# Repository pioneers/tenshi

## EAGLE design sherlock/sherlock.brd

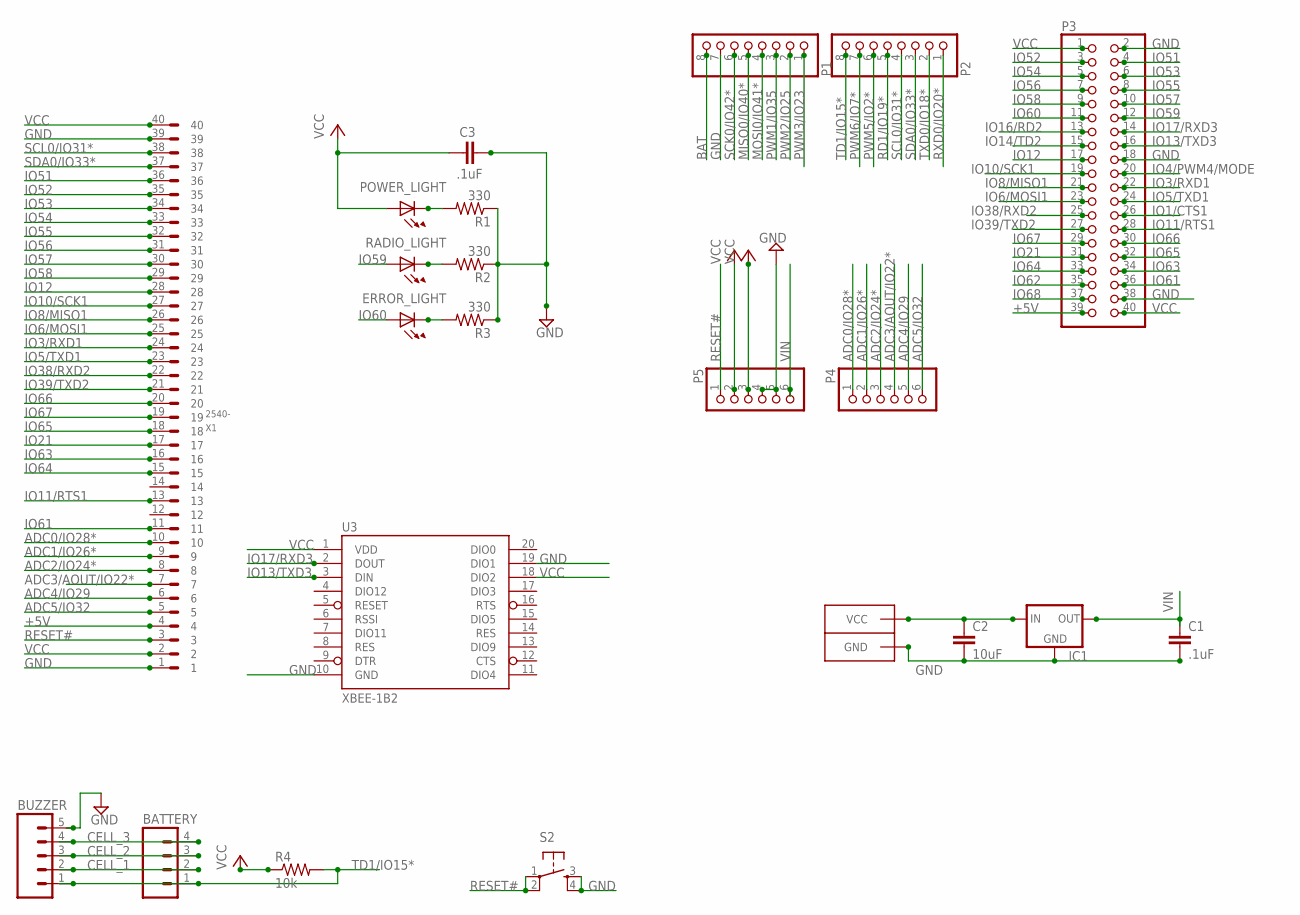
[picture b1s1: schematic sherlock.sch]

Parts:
BATTERY: M041X04-MTA; 1X04-MTA
BUZZER: M05PTH; 1X05
C1, C3: .1uF; 0603-CAP
C2: 10uF; 0603-CAP
ERROR_LIGHT: LED0805; LED-0805
IC1: V_REG_78XXSIDE; 78XXL
P1, P2: PINHD-1X8; 1X08
P3: PINHD-2X20; 2X20
P4, P5: PINHD-1X6; 1X06
POWER: ANDERSONHORIZONTAL; ANDERSON_HORIZONTAL
POWER_LIGHT: LED0805; LED-0805
R1, R2, R3: 330; R0603
R4: 10k; R0603
RADIO_LIGHT: LED0805; LED-0805
S2: TAC_SWITCHPTH; TACTILE-PTH
U3: XBEE-1B2; XBEE-SILK
X1: 2540-; PAK100/2500-40

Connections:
12V: C2.1, IC1.IN, POWER.PIN2 (VCC)
+5V: P3.39, P5.3, X1.4
ADC0/IO28*: P4.1, X1.10
ADC1/IO26*: P4.2, X1.9
ADC2/IO24*: P4.3, X1.8
ADC3/AOUT/IO22*: P4.4, X1.7
ADC4/IO29: P4.5, X1.6
ADC5/IO32: P4.6, X1.5
BAT: P1.8
CELL_1: BATTERY.2, BUZZER.2
CELL_2: BATTERY.3, BUZZER.3
CELL_3: BATTERY.4, BUZZER.4
GND: BUZZER.5, C1.2, C2.2, C3.2, IC1.GND, P1.7, P3.2, P3.18, P3.38, P5.4, P5.5, POWER.PIN1 (GND), R1.1, R2.1, R3.1, S2.3, S2.4, U3.10 (GND), U3.19 (DIO1), X1.1, X1.39
IO1/CTS1: P3.26
IO3/RXD1: P3.22, X1.24
IO4/PWM4/MODE: P3.20
IO5/TXD1: P3.24, X1.23
IO6/MOSI1: P3.23, X1.25
IO8/MISO1: P3.21, X1.26
IO10/SCK1: P3.19, X1.27
IO11/RTS1: P3.28, X1.13
IO12: P3.17, X1.28
IO13/TXD3: P3.16, U3.3 (DIN)
IO14/TD2: P3.15
IO16/RD2: P3.13
IO17/RXD3: P3.14, U3.2 (DOUT)
IO21: P3.31, X1.17
IO38/RXD2: P3.25, X1.22
IO39/TXD2: P3.27, X1.21
IO51: P3.4, X1.36
IO52: P3.3, X1.35
IO53: P3.6, X1.34
IO54: P3.5, X1.33
IO55: P3.8, X1.32
IO56: P3.7, X1.31
IO57: P3.10, X1.30
IO58: P3.9, X1.29
IO59: P3.12, RADIO_LIGHT.A
IO60: ERROR_LIGHT.A, P3.11
IO61: P3.36, X1.11
IO62: P3.35
IO63: P3.34, X1.16
IO64: P3.33, X1.15
IO65: P3.32, X1.18
IO66: P3.30, X1.20
IO67: P3.29, X1.19
IO68: P3.37
MISO0/IO40*: P1.5
MOSI0/IO41*: P1.4
unnamed: POWER_LIGHT.C, R1.2
unnamed: R2.2, RADIO_LIGHT.C
unnamed: ERROR_LIGHT.C, R3.2
PWM1/IO35: P1.3
PWM2/IO25: P1.2
PWM3/IO23: P1.1
PWM5/IO2*: P2.6
PWM6/IO7*: P2.7
RD1/IO19*: P2.5
RESET#: P5.1, S2.1, S2.2, X1.3
RXD0/IO20*: P2.1
SCK0/IO42*: P1.6
SCL0/IO31*: P2.4, X1.38
SDA0/IO33*: P2.3, X1.37
TD1/IO15*: BATTERY.1, BUZZER.1, P2.8, R4.2
TXD0/IO18*: P2.2
VCC: C3.1, P3.1, P3.40, P5.2, POWER_LIGHT.A, R4.1, U3.1 (VDD), U3.18 (DIO2), X1.2, X1.40
VIN: C1.1, IC1.OUT, P5.6

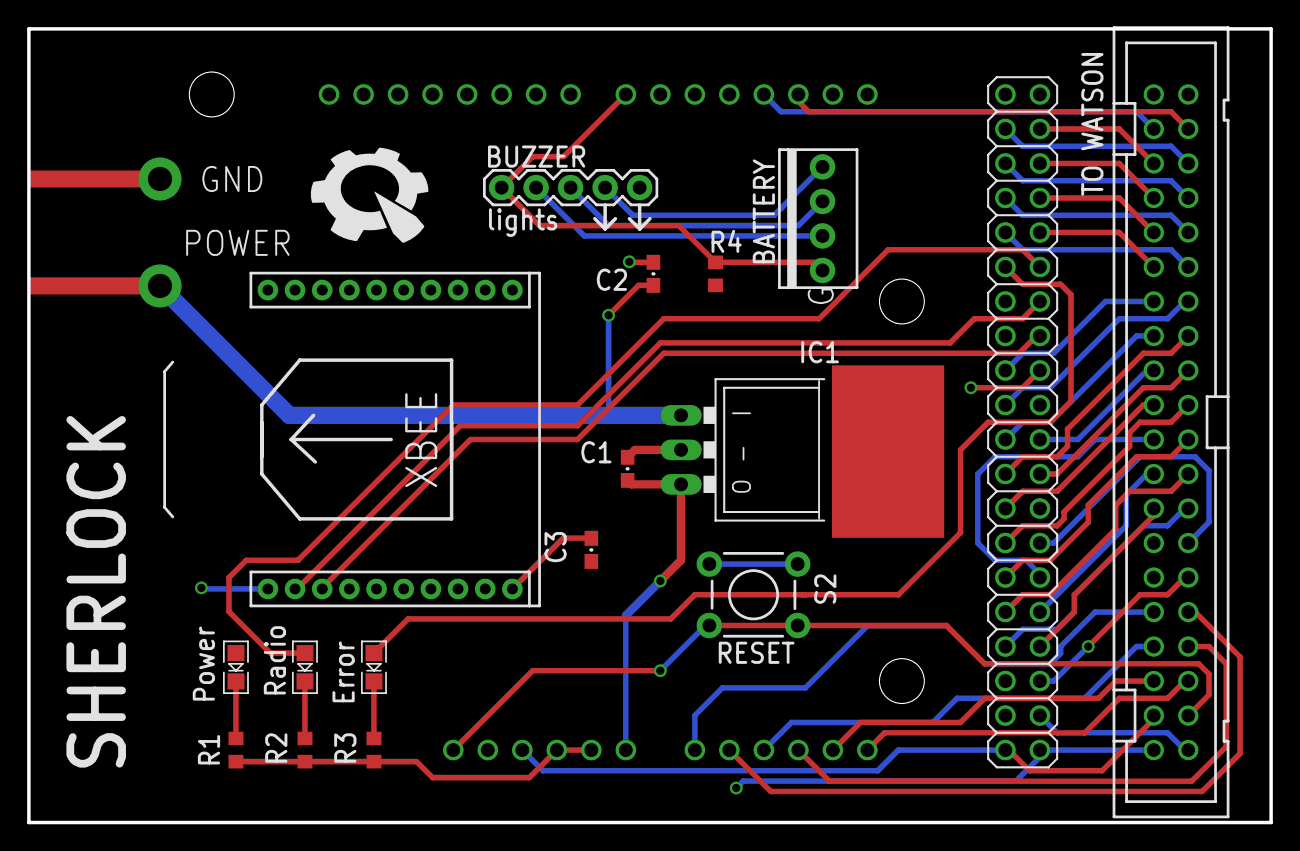
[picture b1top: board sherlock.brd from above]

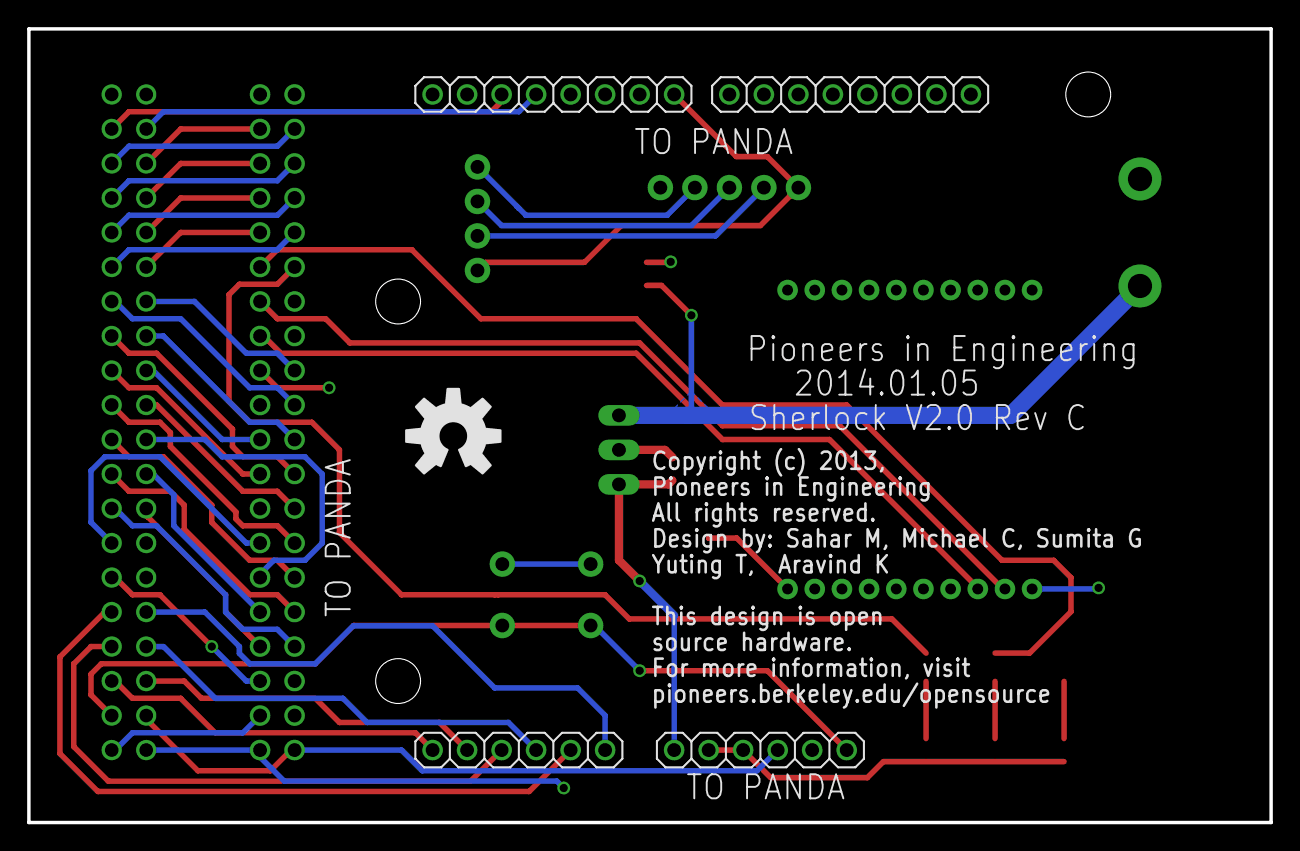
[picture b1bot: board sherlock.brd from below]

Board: 2 copper layers, 91.4 x 58.4 mm, 27 parts (5 on the bottom side), 49 nets.

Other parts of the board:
U$1: PIE-LOGO-SMALL
U$3: Mounting + Test; STAND-OFF
U$4, U$5: Mounting; STAND-OFF
U$7: OSHW-LOGO-L

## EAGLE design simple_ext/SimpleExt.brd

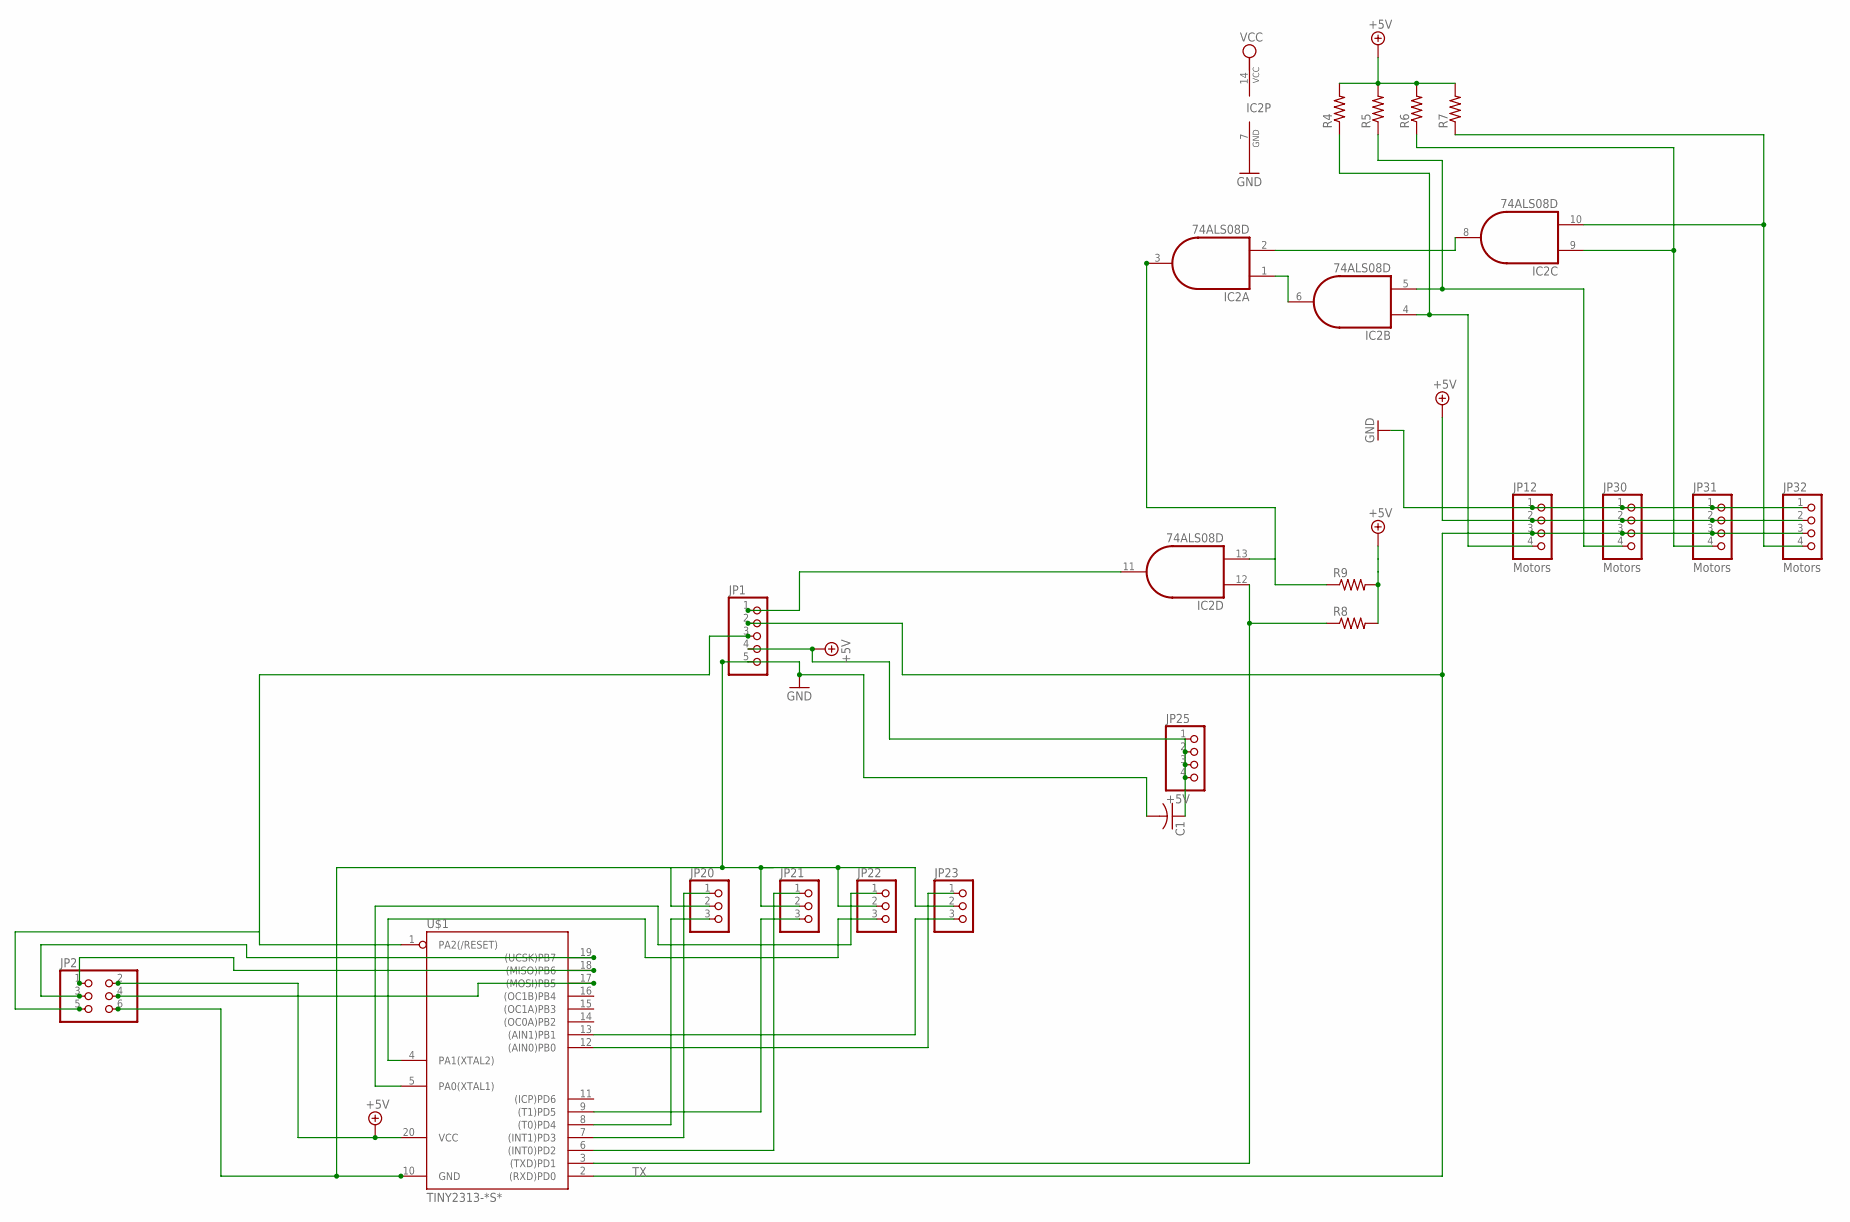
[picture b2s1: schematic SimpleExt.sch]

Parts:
C1: C-USC0603K; C0603K
IC2: 74ALS08D; SO14
JP1: PINHD-1X5; 1X05
JP2: PINHD-2X3; 2X03
JP12, JP30, JP31, JP32: Motors; 1X04-S
JP20, JP21, JP22, JP23: PINHD-1X03_2.54-S; 1X03-S
JP25: +5V; 1X04-S
R4, R5, R6, R7, R8, R9: R-US_R0603; R0603
U$1: TINY2313-*S*; SO20L$

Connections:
+5V: C1.1, JP1.4, JP2.2, JP12.2, JP25.1, JP25.2, JP25.3, JP25.4, JP30.2, JP31.2, JP32.2, R4.2, R5.2, R6.2, R7.2, R8.2, R9.2, U$1.20 (VCC)
GND: C1.2, IC2.7 (GND), JP1.5, JP2.6, JP12.1, JP20.2, JP21.2, JP22.2, JP23.2, JP30.1, JP31.1, JP32.1, U$1.10 (GND)
unnamed: IC2.11 (O), JP1.1
unnamed: JP2.3, U$1.19 ((UCSK)PB7)
unnamed: IC2.10 (I1), JP32.4, R7.1
unnamed: IC2.9 (I0), JP31.4, R6.1
unnamed: JP2.1, U$1.18 ((MISO)PB6)
unnamed: IC2.1 (I0), IC2.6 (O)
unnamed: IC2.2 (I1), IC2.8 (O)
unnamed: IC2.4 (I0), JP12.4, R4.1
unnamed: IC2.12 (I0), R8.1, U$1.3 ((TXD)PD1)
unnamed: JP20.1, U$1.7 ((INT1)PD3)
unnamed: JP21.1, U$1.6 ((INT0)PD2)
unnamed: JP23.3, U$1.13 ((AIN1)PB1)
unnamed: JP20.3, U$1.8 ((T0)PD4)
unnamed: JP21.3, U$1.9 ((T1)PD5)
unnamed: JP2.4, U$1.17 ((MOSI)PB5)
unnamed: JP23.1, U$1.12 ((AIN0)PB0)
unnamed: JP22.3, U$1.4 (PA1(XTAL2))
unnamed: JP22.1, U$1.5 (PA0(XTAL1))
unnamed: IC2.5 (I1), JP30.4, R5.1
RESET#: JP1.3, JP2.5, U$1.1 (PA2(/RESET))
RXD0/IO20*: IC2.3 (O), IC2.13 (I1), R9.1
TX: JP1.2, JP12.3, JP30.3, JP31.3, JP32.3, U$1.2 ((RXD)PD0)
VCC: IC2.14 (VCC)

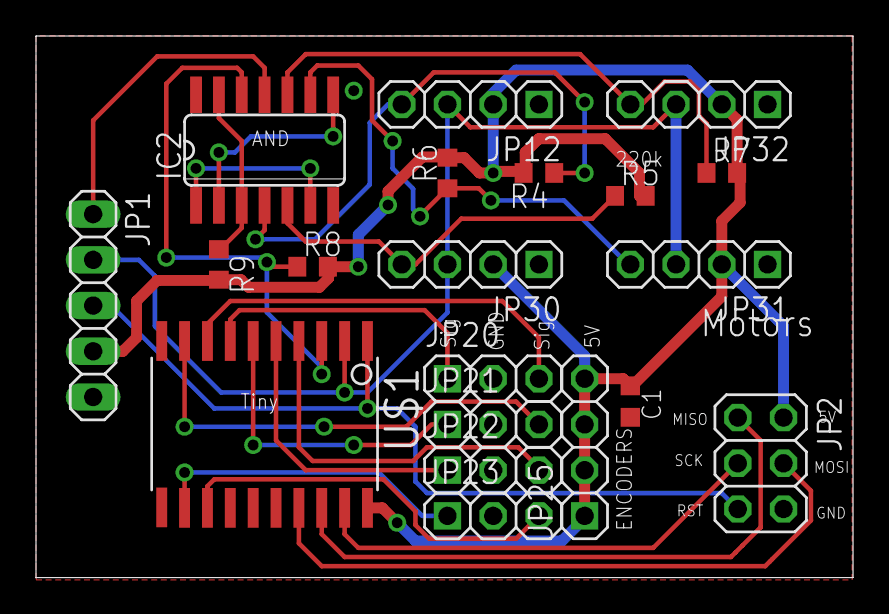
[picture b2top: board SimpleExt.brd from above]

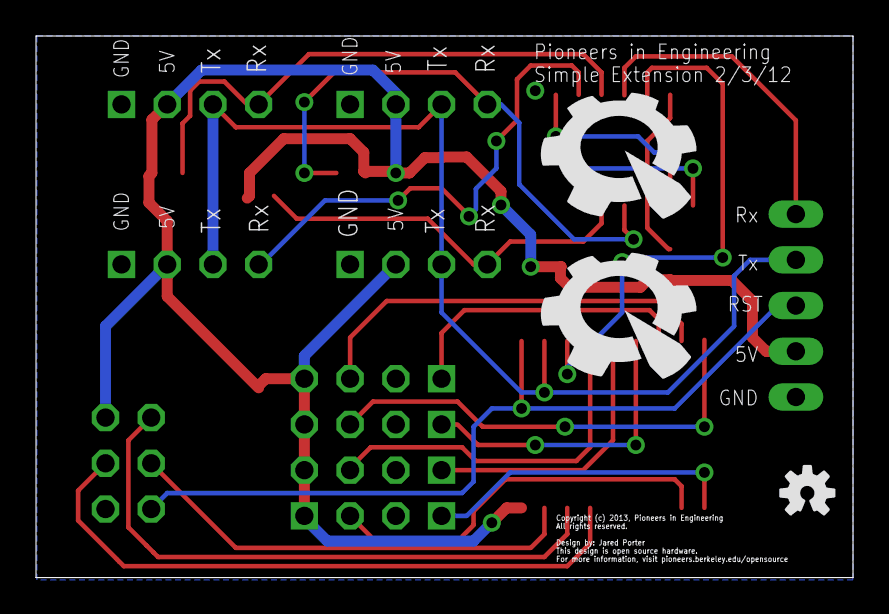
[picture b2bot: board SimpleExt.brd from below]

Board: 2 copper layers, 45.4 x 30.1 mm, 23 parts (3 on the bottom side), 24 nets.

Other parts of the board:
U$2: OSHW-LOGO-S
U$5, U$6: PIE-LOGO-SMALL

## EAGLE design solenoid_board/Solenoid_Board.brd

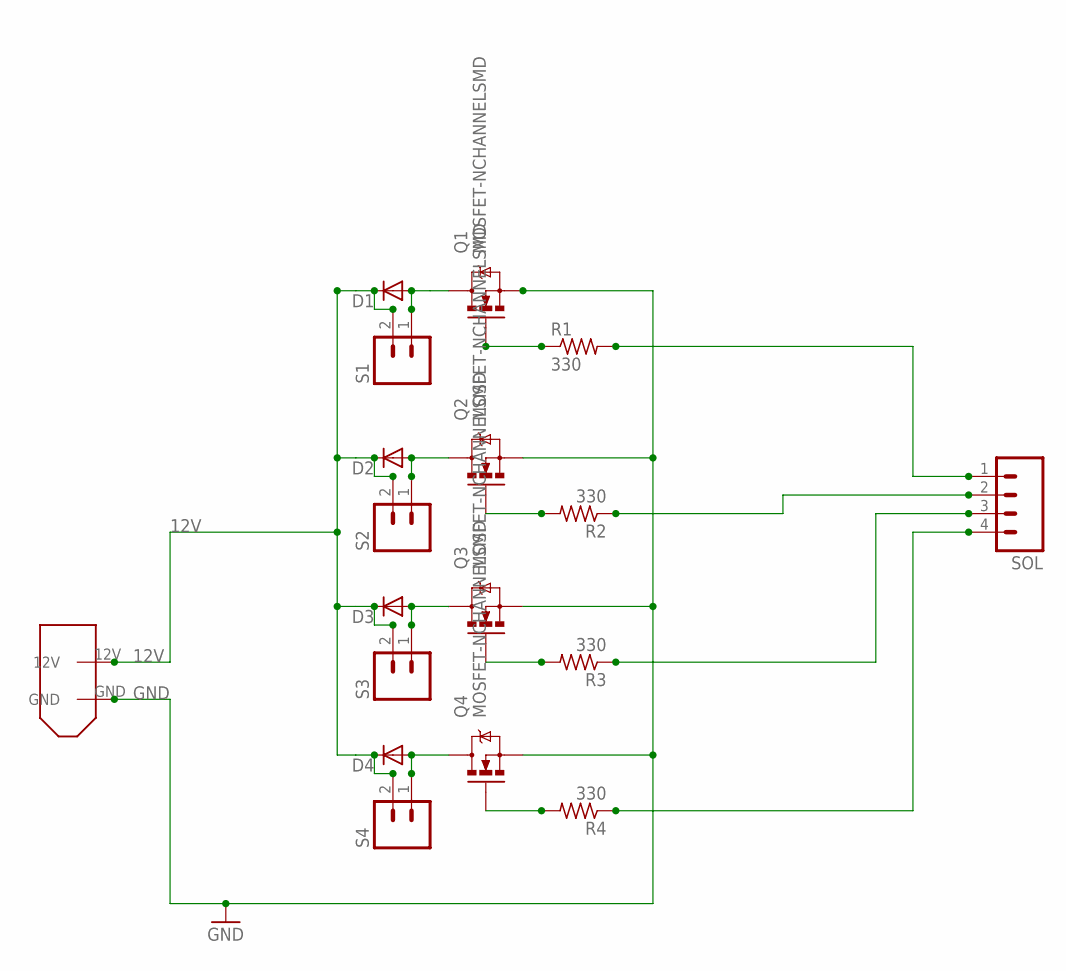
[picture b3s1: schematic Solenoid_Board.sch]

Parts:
D1, D2, D3, D4: DIODESMA-ALT; SMA-DIODE_ALT
Q1, Q2, Q3, Q4: MOSFET-NCHANNELSMD; SOT23-3
R1, R2, R3, R4: 330; R0603
S1, S2, S3, S4: M02; 1X02
SOL: M04; 1X04
U$2: XT60CONNECTOR

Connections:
12V: D1.C, D2.C, D3.C, D4.C, S1.2, S2.2, S3.2, S4.2, U$2.12V
GND: Q1.2 (S), Q2.2 (S), Q3.2 (S), Q4.2 (S), U$2.GND
unnamed: R1.2, SOL.1
unnamed: D1.A, Q1.3 (D), S1.1
unnamed: D4.A, Q4.3 (D), S4.1
unnamed: D3.A, Q3.3 (D), S3.1
unnamed: R2.1, SOL.2
unnamed: R3.1, SOL.3
unnamed: R4.1, SOL.4
unnamed: D2.A, Q2.3 (D), S2.1
unnamed: Q1.1 (G), R1.1
unnamed: Q2.1 (G), R2.2
unnamed: Q3.1 (G), R3.2
unnamed: Q4.1 (G), R4.2

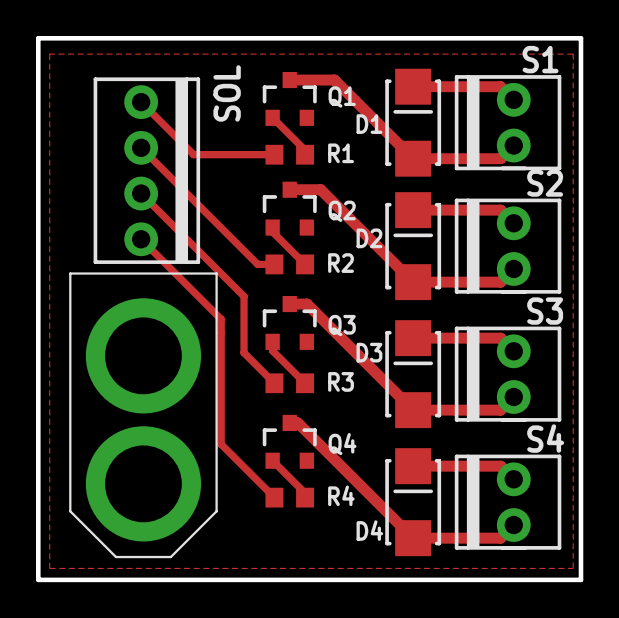
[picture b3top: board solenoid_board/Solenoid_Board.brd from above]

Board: 2 copper layers, 30.1 x 30.1 mm, 19 parts (1 on the bottom side), 14 nets.

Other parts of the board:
U$1: PIE-LOGO-SMALL

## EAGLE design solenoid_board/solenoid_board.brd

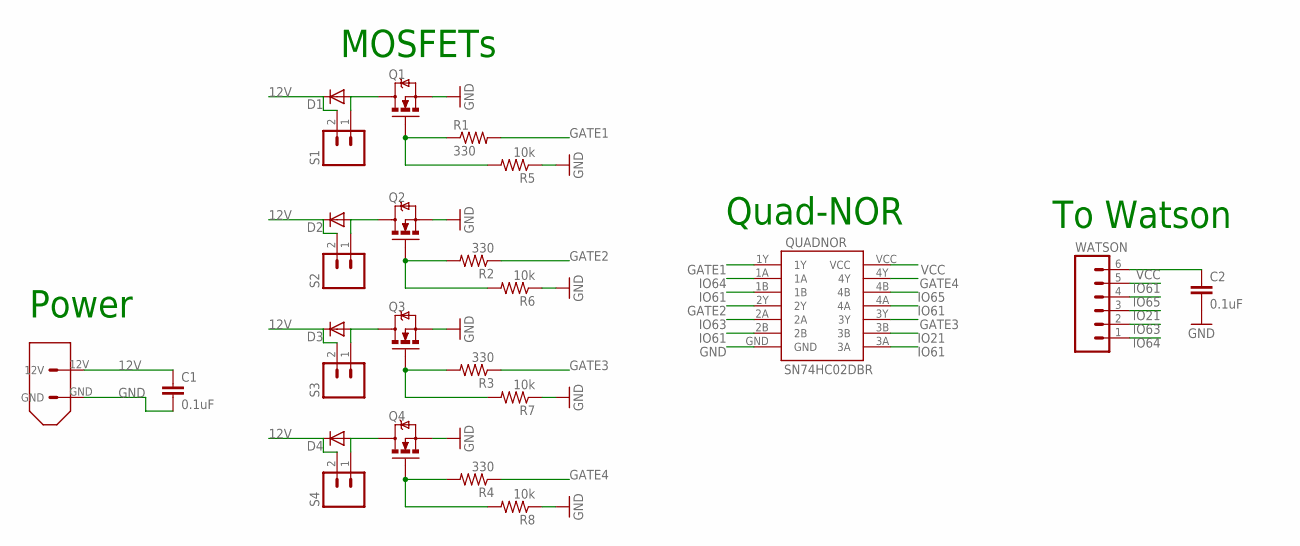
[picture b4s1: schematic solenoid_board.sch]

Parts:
C1, C2: 0.1uF; 0603-CAP
D1, D2, D3, D4: DIODESMA-ALT; SMA-DIODE_ALT
Q1, Q2, Q3, Q4: MOSFET-NCHANNELSMD; SOT23-3
QUADNOR: SN74HC02DBR; QUADNOR
R1, R2, R3, R4: 330; R0603
R5, R6, R7, R8: 10k; R0603
S1, S2, S3, S4: M021X02-MTA; 1X02-MTA
U$2: XT60CONNECTOR
WATSON: M06; 1X06-MTA

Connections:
12V: C1.1, D1.C, D2.C, D3.C, D4.C, S1.2, S2.2, S3.2, S4.2, U$2.12V
GATE1: QUADNOR.1Y, R1.2
GATE2: QUADNOR.2Y, R2.1
GATE3: QUADNOR.3Y, R3.1
GATE4: QUADNOR.4Y, R4.1
GND: C1.2, C2.2, Q1.2 (S), Q2.2 (S), Q3.2 (S), Q4.2 (S), QUADNOR.GND, R5.1, R6.1, R7.1, R8.1, U$2.GND
IO21: QUADNOR.3B, WATSON.3
IO61: QUADNOR.1B, QUADNOR.2B, QUADNOR.3A, QUADNOR.4A, WATSON.5
IO63: QUADNOR.2A, WATSON.2
IO64: QUADNOR.1A, WATSON.1
IO65: QUADNOR.4B, WATSON.4
unnamed: D1.A, Q1.3 (D), S1.1
unnamed: D4.A, Q4.3 (D), S4.1
unnamed: D3.A, Q3.3 (D), S3.1
unnamed: D2.A, Q2.3 (D), S2.1
unnamed: Q1.1 (G), R1.1, R5.2
unnamed: Q2.1 (G), R2.2, R6.2
unnamed: Q3.1 (G), R3.2, R7.2
unnamed: Q4.1 (G), R4.2, R8.2
VCC: C2.1, QUADNOR.VCC, WATSON.6

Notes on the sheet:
Power
Quad-NOR
To Watson
MOSFETs

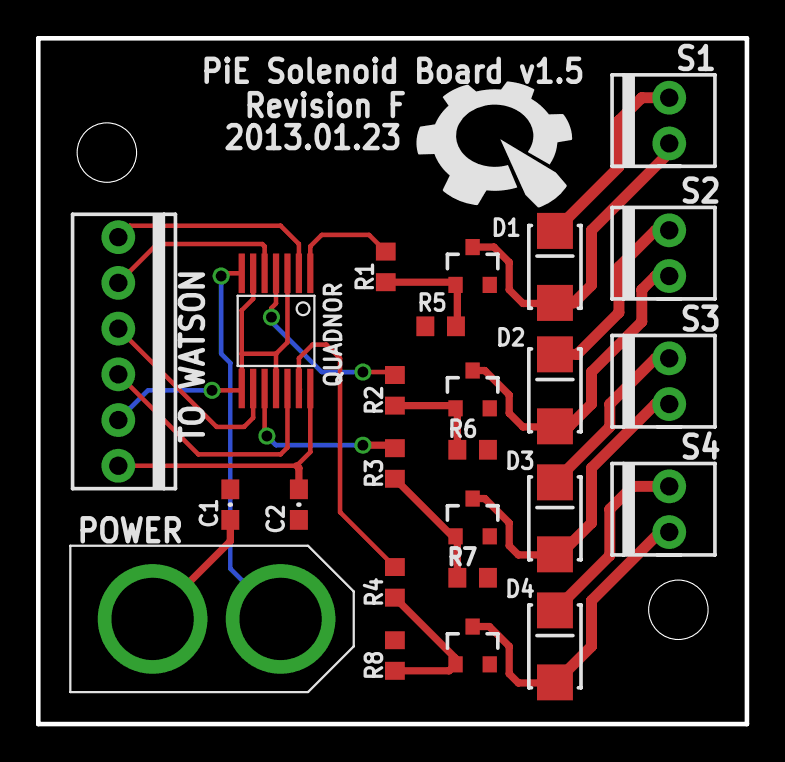
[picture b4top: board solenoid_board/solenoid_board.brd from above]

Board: 2 copper layers, 39.4 x 38.1 mm, 29 parts (1 on the bottom side), 20 nets.

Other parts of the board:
U$1: PIE-LOGO-SMALL
U$3, U$4: Mounting + Test; STAND-OFF
U$5: OSHW-LOGO-M

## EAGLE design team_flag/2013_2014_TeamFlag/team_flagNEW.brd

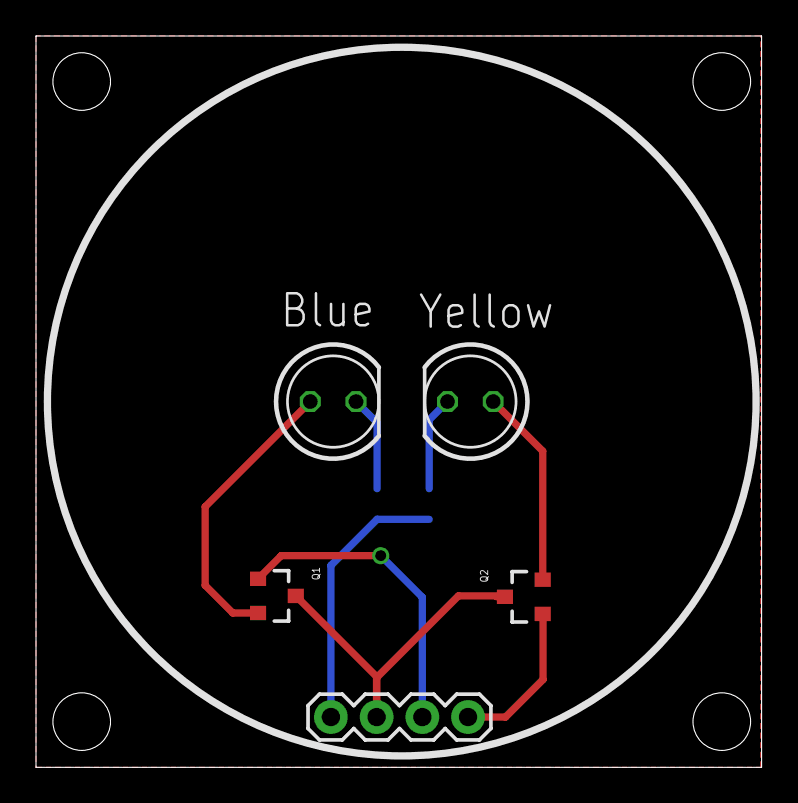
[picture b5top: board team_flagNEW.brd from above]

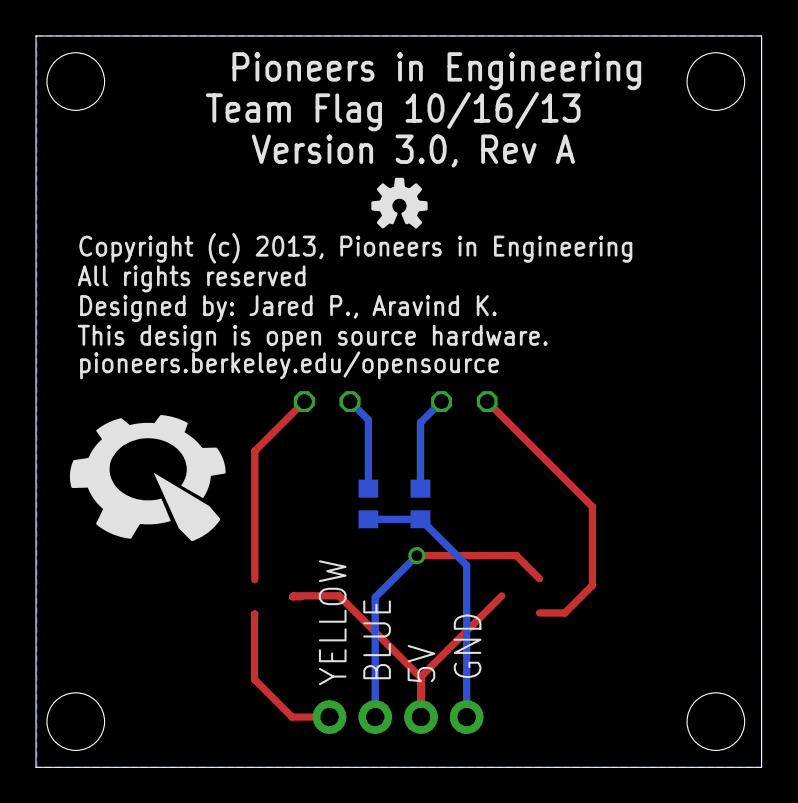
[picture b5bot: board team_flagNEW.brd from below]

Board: 2 copper layers, 40.3 x 40.6 mm, 9 parts (4 on the bottom side), 8 nets.

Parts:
JP1: 1X04
LED1, LED2: LED5MM
Q1, Q2: MOSFET-NCHANNELSMD; SOT23-3
R1, R2: 330; R0603
U$1: PIE-LOGO-SMALL
U$2: OSHW-LOGO-S

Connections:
5V: JP1.2, Q1.3, Q2.3
BDRAIN: LED1.K, R1.2
BLUE: JP1.3, Q1.1
BSIGNAL: LED1.A, Q1.2
GND: JP1.1, R1.1, R2.1
YDRAIN: LED2.K, R2.2
YELLOW: JP1.4, Q2.1
YSIGNAL: LED2.A, Q2.2

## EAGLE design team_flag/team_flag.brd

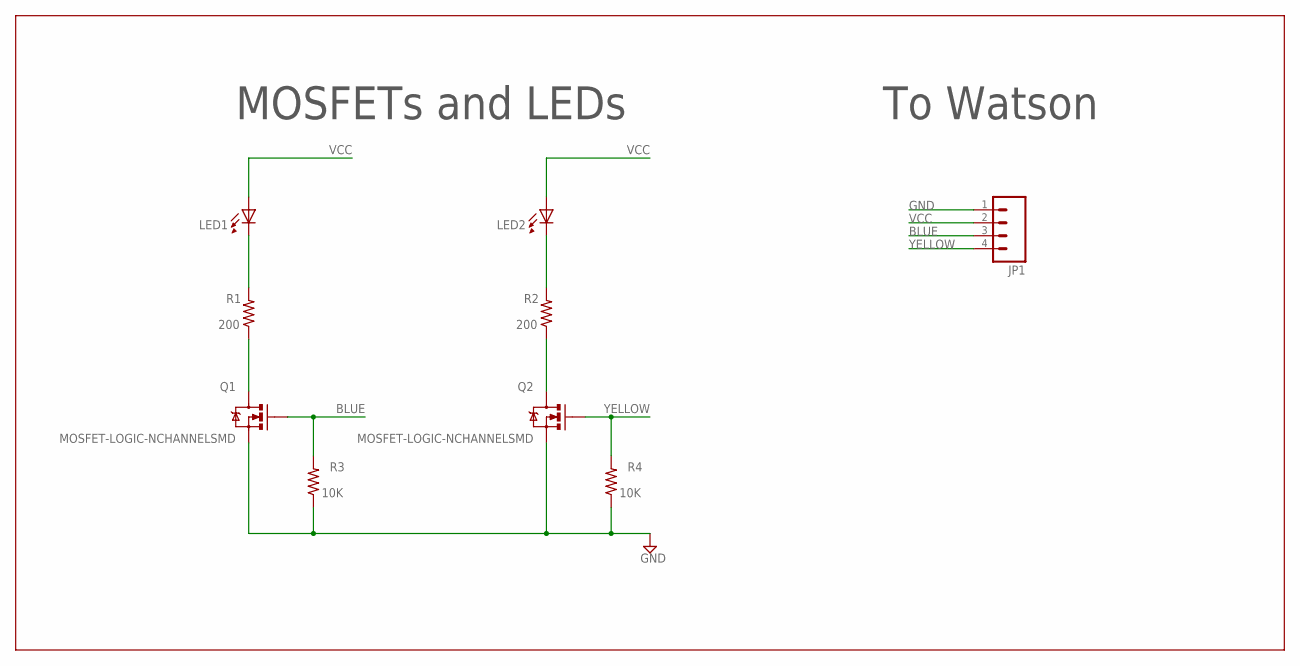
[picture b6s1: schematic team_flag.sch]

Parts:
JP1: M041X04-MTA; 1X04-MTA
LED1, LED2: LEDLED5MM-NOFLAT; LED5MM-NOFLAT
Q1, Q2: MOSFET-LOGIC-NCHANNELSMD; SOT23-3-LOGIC
R1, R2: 200; R0603
R3, R4: 10K; R0603

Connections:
BLUE: JP1.3, Q1.1 (G), R3.2
BSOURCE: Q1.3 (D), R1.1
GND: JP1.1, Q1.2 (S), Q2.2 (S), R3.1, R4.1
unnamed: LED1.K (C), R1.2
unnamed: LED2.K (C), R2.2
VCC: JP1.2, LED1.A, LED2.A
YELLOW: JP1.4, Q2.1 (G), R4.2
YSOURCE: Q2.3 (D), R2.1

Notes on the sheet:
To Watson
MOSFETs and LEDs

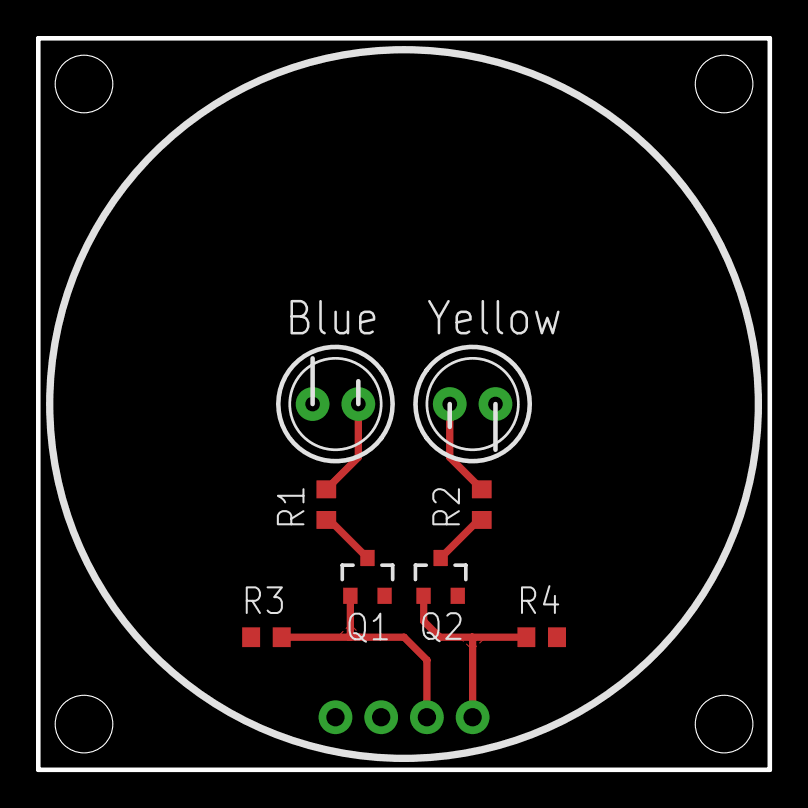
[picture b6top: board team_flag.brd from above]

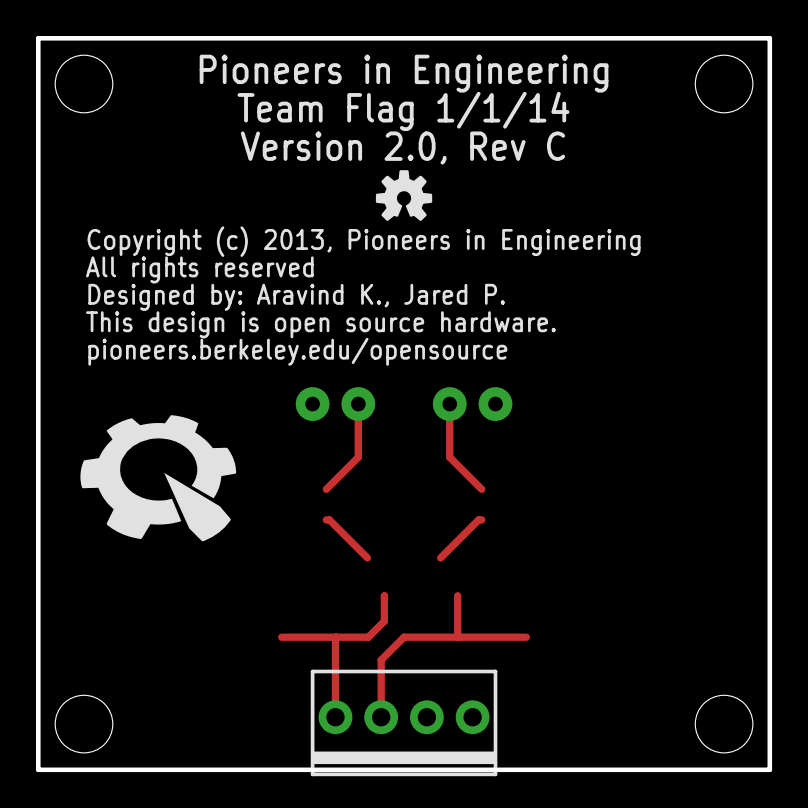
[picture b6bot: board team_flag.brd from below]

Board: 2 copper layers, 40.6 x 40.6 mm, 11 parts (3 on the bottom side), 8 nets.

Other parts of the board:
U$1: PIE-LOGO-SMALL
U$2: OSHW-LOGO-S

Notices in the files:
sherlock/sherlock.brd:
Copyright (c) 2013,
Pioneers in Engineering
All rights reserved.
simple_ext/SimpleExt.brd:
Copyright (c) 2013, Pioneers in Engineering
